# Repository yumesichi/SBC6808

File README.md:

#SBC6808
を作る
ブログは
https://sbc6808.blogspot.com/

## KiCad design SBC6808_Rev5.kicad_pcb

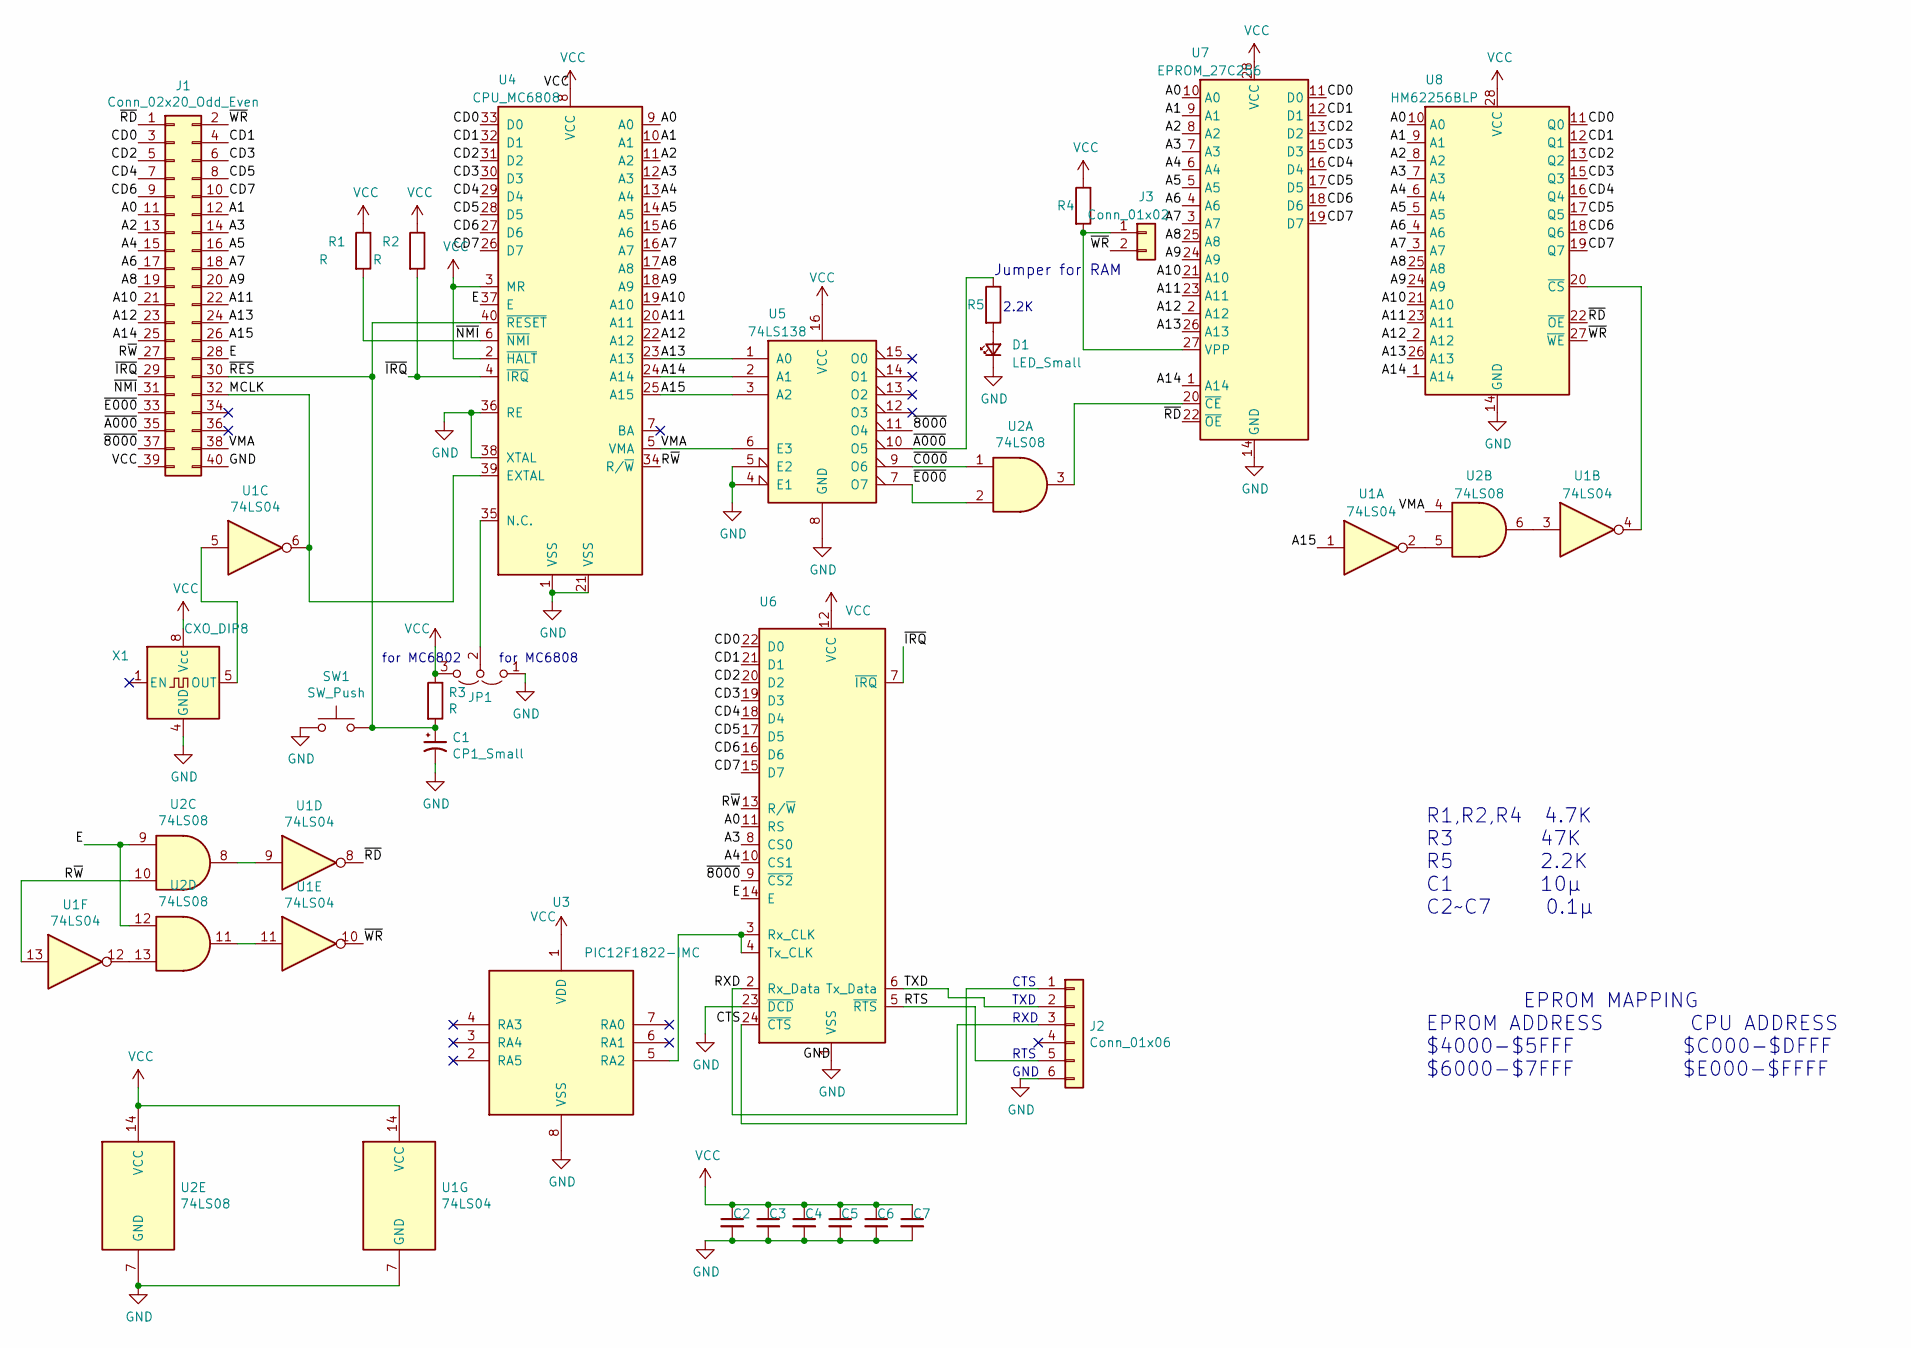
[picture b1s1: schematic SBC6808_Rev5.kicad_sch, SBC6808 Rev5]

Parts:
C1: CP1_Small; CP_Radial_D5.0mm_P2.50mm
C2, C3, C4, C5, C6, C7: My_Device_C_Small; C_Disc_D4.3mm_W1.9mm_P5.00mm
D1: LED_Small; LED_D3.0mm
J1: Conn_02x20_Odd_Even; IDC-Header_2x20_P2.54mm_Horizontal
J2: Conn_01x06; PinHeader_1x06_P2.54mm_Horizontal
J3: Conn_01x02; PinHeader_1x02_P2.54mm_Vertical
JP1: PinHeader_1x03_P2.54mm_Vertical
R1, R2, R3, R4, R5: R; R_Axial_DIN0204_L3.6mm_D1.6mm_P5.08mm_Horizontal
SW1: SW_Push; SW_PUSH_6mm_H4.3mm
U1: 74LS04; DIP-14_W7.62mm_Socket
U2: 74LS08; DIP-14_W7.62mm_Socket
U3: PIC12F1822-IMC; DIP-8_W7.62mm
U4: CPU_MC6808; DIP-40_W15.24mm
U5: 74LS138; DIP-16_W7.62mm_Socket
U6: SBC6808_Rev3-rescue_MC6850-Interface_UART-SBC6808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; DIP-24_W15.24mm_Socket
U7: EPROM_27C256; DIP-28_W15.24mm
U8: HM62256BLP; DIP-28_W15.24mm
X1: CXO_DIP8; Oscillator_DIP-8

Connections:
/A0: J1.11, U4.9 (A0), U6.11 (RS), U7.10 (A0), U8.10 (A0)
/A1: J1.12, U4.10 (A1), U7.9 (A1), U8.9 (A1)
/A2: J1.13, U4.11 (A2), U7.8 (A2), U8.8 (A2)
/A3: J1.14, U4.12 (A3), U6.8 (CS0), U7.7 (A3), U8.7 (A3)
/A4: J1.15, U4.13 (A4), U6.10 (CS1), U7.6 (A4), U8.6 (A4)
/A5: J1.16, U4.14 (A5), U7.5 (A5), U8.5 (A5)
/A6: J1.17, U4.15 (A6), U7.4 (A6), U8.4 (A6)
/A7: J1.18, U4.16 (A7), U7.3 (A7), U8.3 (A7)
/A8: J1.19, U4.17 (A8), U7.25 (A8), U8.25 (A8)
/A9: J1.20, U4.18 (A9), U7.24 (A9), U8.24 (A9)
/A10: J1.21, U4.19 (A10), U7.21 (A10), U8.21 (A10)
/A11: J1.22, U4.20 (A11), U7.23 (A11), U8.23 (A11)
/A12: J1.23, U4.22 (A12), U7.2 (A12), U8.2 (A12)
/A13: J1.24, U4.23 (A13), U5.1 (A0), U7.26 (A13), U8.26 (A13)
/A14: J1.25, U4.24 (A14), U5.2 (A1), U7.1 (A14), U8.1 (A14)
/A15: J1.26, U1.1, U4.25 (A15), U5.3 (A2)
/CD0: J1.3, U4.33 (D0), U6.22 (D0), U7.11 (D0), U8.11 (Q0)
/CD1: J1.4, U4.32 (D1), U6.21 (D1), U7.12 (D1), U8.12 (Q1)
/CD2: J1.5, U4.31 (D2), U6.20 (D2), U7.13 (D2), U8.13 (Q2)
/CD3: J1.6, U4.30 (D3), U6.19 (D3), U7.15 (D3), U8.15 (Q3)
/CD4: J1.7, U4.29 (D4), U6.18 (D4), U7.16 (D4), U8.16 (Q4)
/CD5: J1.8, U4.28 (D5), U6.17 (D5), U7.17 (D5), U8.17 (Q5)
/CD6: J1.9, U4.27 (D6), U6.16 (D6), U7.18 (D6), U8.18 (Q6)
/CD7: J1.10, U4.26 (D7), U6.15 (D7), U7.19 (D7), U8.19 (Q7)
/CTS: J2.1, U6.24 (~CTS)
/E: J1.28, U2.9, U2.12, U4.37 (E), U6.14 (E)
/MCLK: J1.32, U1.6, U4.39 (EXTAL)
/RTS: J2.5, U6.5 (~RTS)
/RXD: J2.3, U6.2 (Rx_Data)
/R~W: J1.27, U1.13, U2.10, U4.34 (R/~W), U6.13 (R/~W)
/TXD: J2.2, U6.6 (Tx_Data)
/VMA: J1.38, U2.4, U4.5 (VMA), U5.6 (E3)
/~8000: J1.37, U5.11 (O4), U6.9 (~CS2)
/~A000: J1.35, R5.1, U5.10 (O5)
/~C000: U2.1, U5.9 (O6)
/~E000: J1.33, U2.2, U5.7 (O7)
/~IRQ: J1.29, R2.2, U4.4 (~IRQ), U6.7 (~IRQ)
/~NMI: J1.31, R1.2, U4.6 (~NMI)
/~RD: J1.1, U1.8, U7.22 (~OE), U8.22 (~OE)
/~RES: C1.1, J1.30, R3.2, SW1.2, U4.40 (~RESET)
/~WR: J1.2, J3.2, U1.10, U8.27 (~WE)
GND: C1.2, C2.2, C3.2, C4.2, C5.2, C6.2, C7.2, D1.1 (K), J1.40, J2.6, JP1.1 (A), SW1.1, U1.7 (GND), U2.7 (GND), U3.8 (VSS), U4.1 (VSS), U4.21 (VSS), U4.36 (RE), U4.38 (XTAL), U5.4 (E1), U5.5 (E2), U5.8 (GND), U6.1 (VSS), U6.23 (~DCD), U7.14 (GND), U8.14 (GND), X1.4 (GND)
unnamed: D1.2 (A), R5.2
unnamed: J3.1, R4.2, U7.27 (VPP)
unnamed: JP1.2 (C), U4.35 (N.C.)
unnamed: U1.2, U2.5
unnamed: U1.3, U2.6
unnamed: U1.9, U2.8
unnamed: U1.11, U2.11
unnamed: U1.12, U2.13
unnamed: U3.5 (RA2), U6.3 (Rx_CLK), U6.4 (Tx_CLK)
unnamed: U2.3, U7.20 (~CE)
unnamed: U1.4, U8.20 (~CS)
unnamed: U1.5, X1.5 (OUT)
VCC: C2.1, C3.1, C4.1, C5.1, C6.1, C7.1, J1.39, JP1.3 (B), R1.1, R2.1, R3.1, R4.1, U1.14 (VCC), U2.14 (VCC), U3.1 (VDD), U4.2 (~HALT), U4.3 (MR), U4.8 (VCC), U5.16 (VCC), U6.12 (VCC), U7.28 (VCC), U8.28 (VCC), X1.8 (Vcc)

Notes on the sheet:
GND
R1,R2,R4 4.7K R3 47K R5 2.2K C1 10μ C2~C7 0.1μ
for MC6802
for MC6808
CTS
RXD
TXD
Jumper for RAM
EPROM MAPPING EPROM ADDRESS CPU ADDRESS $4000-$5FFF $C000-$DFFF $6000-$7FFF $E000-$FFFF
2.2K
RTS

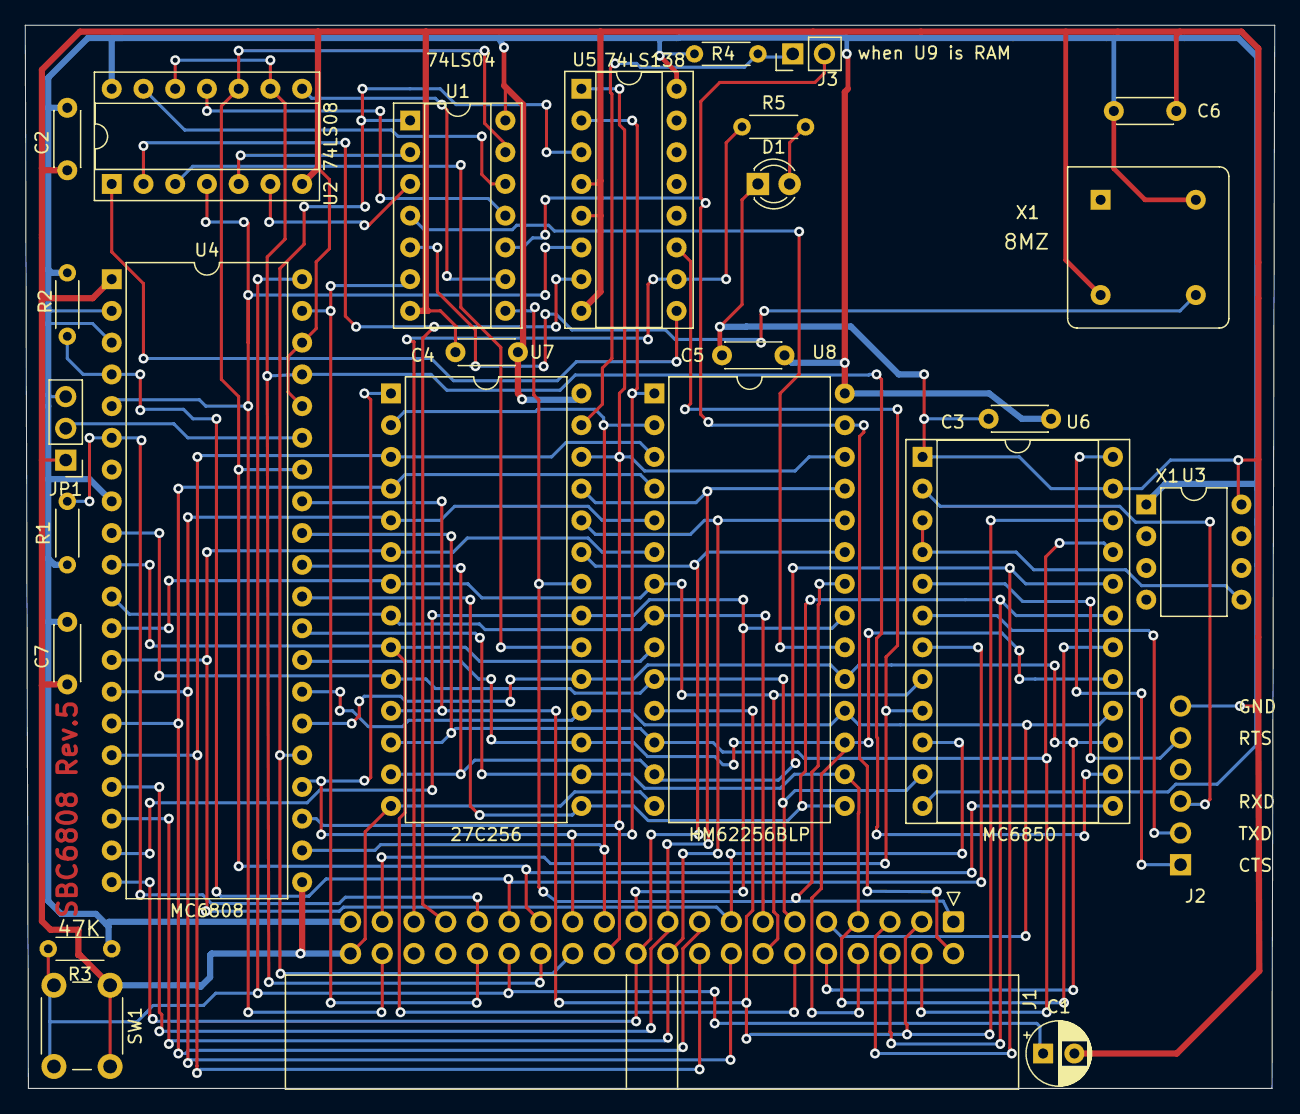
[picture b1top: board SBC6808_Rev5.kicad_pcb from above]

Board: 2 copper layers, 100.0 x 85.1 mm, 27 parts (1 on the bottom side), 55 nets.
